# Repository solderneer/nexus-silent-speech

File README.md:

# Nexus, a session-independent silent speech interface
A novel approach to session-independent silent speech recognition systems with a multiplexed star electrode array, developed for my final year dissertation at University College London (UCL). Includes datasets, code, and electronics CAD files.

## Overview
This repository houses my final year dissertation project at University College London (UCL), focused on developing a novel multiplexed star electrode array to address the challenges of cross-session variability in silent speech recognition systems. This innovative approach leverages configurable electrode orientations to significantly enhance the signal-to-noise ratio (SNR) of surface electromyography (sEMG) signals, leading to improved recognition accuracy across sessions.

## Project Objectives
- To investigate the impact of cross-session variability on the accuracy of silent speech recognition systems.
- To design, develop, and evaluate a multiplexed star electrode array capable of adjusting electrode orientations for optimal muscle-electrode alignment.
- To compare the performance of the novel star electrode array against traditional electrode configurations in terms of SNR and silent speech recognition accuracy.

## Results Summary
The project successfully demonstrated the potential of the star electrode array to achieve superior muscle-electrode alignment, resulting in a significant increase in SNR compared to control configurations. Most notably, the array displayed a remarkable 41% relative improvement in cross-session classification accuracy, underscoring its effectiveness in mitigating the challenges posed by session-dependent variability.

## Contents
- `datasets/`: Contains the sEMG datasets collected during the project, across multiple sessions and with different electrode configurations.
- `code/`: Includes all code developed for signal acquisition, signal processing, feature extraction, and classification tasks.
- `cad/`: Houses the electronics CAD files for the star electrode array and control circuitry, enabling replication and further research.
- `docs/`: Additional project documentation, including project report and presentation slides.

## Contact
For any inquiries or collaboration proposals, please contact [Shan](https://solderneer.me) at [sudhar393@gmail.com](mailto://sudhar393@gmail.com).

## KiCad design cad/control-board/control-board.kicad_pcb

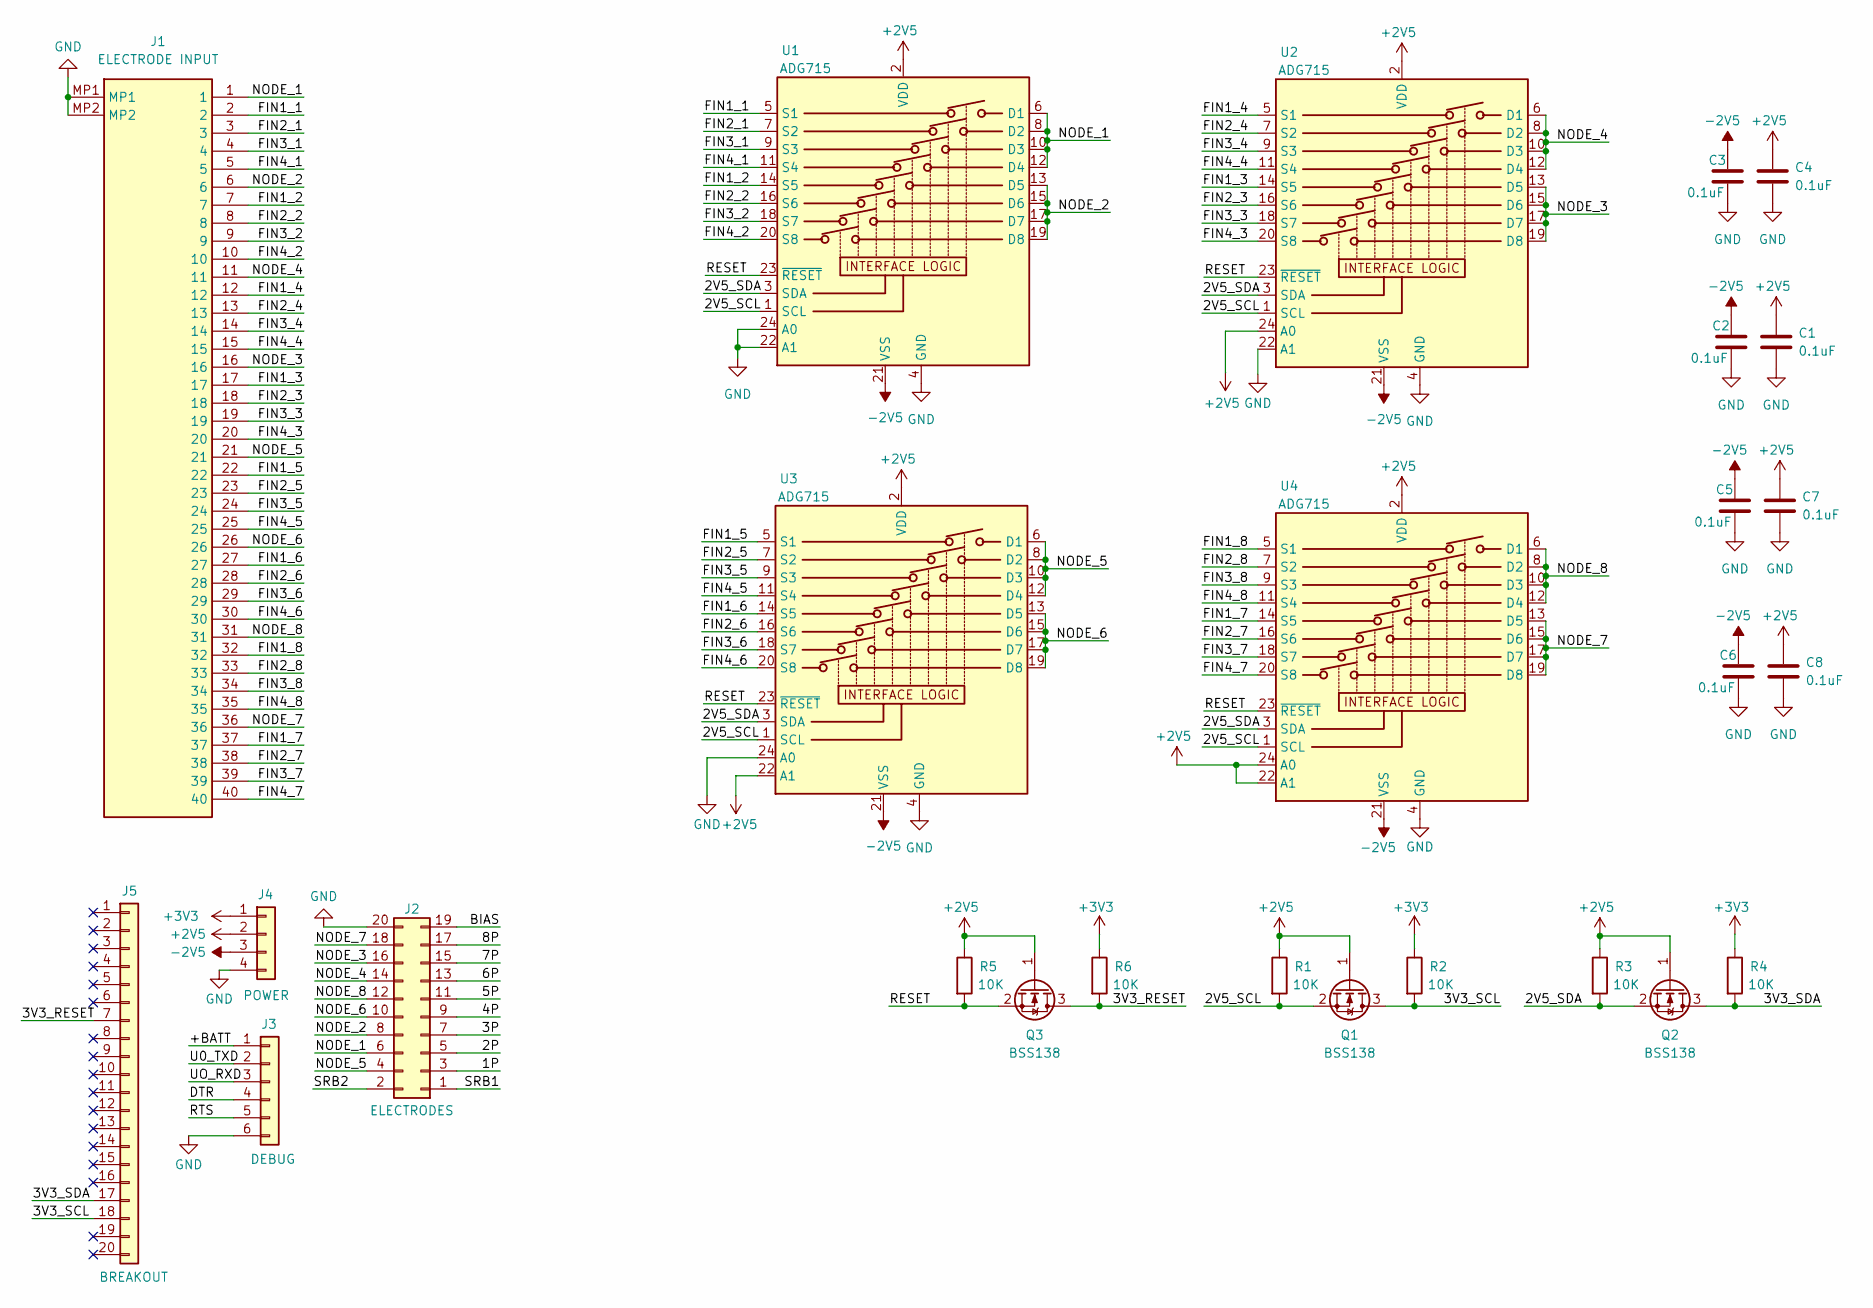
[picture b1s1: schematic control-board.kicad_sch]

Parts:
C1, C2, C3, C4, C5, C6, C7, C8: 0.1uF; C_0603_1608Metric
J1: ELECTRODE INPUT; F32D1A7Y121040; Manufacturer_Part_Number F32D-1A7Y1-21040
J2: ELECTRODES; PinHeader_2x10_P2.54mm_Vertical
J3: DEBUG; PinHeader_1x06_P2.54mm_Vertical
J4: POWER; PinHeader_1x04_P2.54mm_Vertical
J5: BREAKOUT; PinHeader_1x20_P2.54mm_Vertical
Q1, Q2, Q3: BSS138; SOT-23
R1, R2, R3, R4, R5, R6: 10K; R_0603_1608Metric
U1, U2, U3, U4: ADG715; TSSOP-24_4.4x7.8mm_P0.65mm

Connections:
+2V5: C1.1, C4.1, C7.1, C8.1, J4.2, Q1.1 (G), Q2.1 (G), Q3.1 (G), R1.1, R3.1, R5.1, U1.2 (VDD), U2.2 (VDD), U2.24 (A0), U3.2 (VDD), U3.22 (A1), U4.2 (VDD), U4.22 (A1), U4.24 (A0)
+3V3: J4.1, R2.1, R4.1, R6.1
-2V5: C2.1, C3.1, C5.1, C6.1, J4.3, U1.21 (VSS), U2.21 (VSS), U3.21 (VSS), U4.21 (VSS)
/1P: J2.3
/2P: J2.5
/2V5_SCL: Q1.2 (S), R1.2, U1.1 (SCL), U2.1 (SCL), U3.1 (SCL), U4.1 (SCL)
/2V5_SDA: Q2.2 (S), R3.2, U1.3 (SDA), U2.3 (SDA), U3.3 (SDA), U4.3 (SDA)
/3P: J2.7
/3V3_RESET: J5.7, Q3.3 (D), R6.2
/3V3_SCL: J5.18, Q1.3 (D), R2.2
/3V3_SDA: J5.17, Q2.3 (D), R4.2
/4P: J2.9
/5P: J2.11
/6P: J2.13
/7P: J2.15
/8P: J2.17
/+BATT: J3.1
/BIAS: J2.19
/DTR: J3.4
/FIN1_1: J1.2, U1.5 (S1)
/FIN1_2: J1.7, U1.14 (S5)
/FIN1_3: J1.17, U2.14 (S5)
/FIN1_4: J1.12, U2.5 (S1)
/FIN1_5: J1.22, U3.5 (S1)
/FIN1_6: J1.27, U3.14 (S5)
/FIN1_7: J1.37, U4.14 (S5)
/FIN1_8: J1.32, U4.5 (S1)
/FIN2_1: J1.3, U1.7 (S2)
/FIN2_2: J1.8, U1.16 (S6)
/FIN2_3: J1.18, U2.16 (S6)
/FIN2_4: J1.13, U2.7 (S2)
/FIN2_5: J1.23, U3.7 (S2)
/FIN2_6: J1.28, U3.16 (S6)
/FIN2_7: J1.38, U4.16 (S6)
/FIN2_8: J1.33, U4.7 (S2)
/FIN3_1: J1.4, U1.9 (S3)
/FIN3_2: J1.9, U1.18 (S7)
/FIN3_3: J1.19, U2.18 (S7)
/FIN3_4: J1.14, U2.9 (S3)
/FIN3_5: J1.24, U3.9 (S3)
/FIN3_6: J1.29, U3.18 (S7)
/FIN3_7: J1.39, U4.18 (S7)
/FIN3_8: J1.34, U4.9 (S3)
/FIN4_1: J1.5, U1.11 (S4)
/FIN4_2: J1.10, U1.20 (S8)
/FIN4_3: J1.20, U2.20 (S8)
/FIN4_4: J1.15, U2.11 (S4)
/FIN4_5: J1.25, U3.11 (S4)
/FIN4_6: J1.30, U3.20 (S8)
/FIN4_7: J1.40, U4.20 (S8)
/FIN4_8: J1.35, U4.11 (S4)
/NODE_1: J1.1, J2.6, U1.6 (D1), U1.8 (D2), U1.10 (D3), U1.12 (D4)
/NODE_2: J1.6, J2.8, U1.13 (D5), U1.15 (D6), U1.17 (D7), U1.19 (D8)
/NODE_3: J1.16, J2.16, U2.13 (D5), U2.15 (D6), U2.17 (D7), U2.19 (D8)
/NODE_4: J1.11, J2.14, U2.6 (D1), U2.8 (D2), U2.10 (D3), U2.12 (D4)
/NODE_5: J1.21, J2.4, U3.6 (D1), U3.8 (D2), U3.10 (D3), U3.12 (D4)
/NODE_6: J1.26, J2.10, U3.13 (D5), U3.15 (D6), U3.17 (D7), U3.19 (D8)
/NODE_7: J1.36, J2.18, U4.13 (D5), U4.15 (D6), U4.17 (D7), U4.19 (D8)
/NODE_8: J1.31, J2.12, U4.6 (D1), U4.8 (D2), U4.10 (D3), U4.12 (D4)
/RESET: Q3.2 (S), R5.2, U1.23 (~RESET), U2.23 (~RESET), U3.23 (~RESET), U4.23 (~RESET)
/RTS: J3.5
/SRB1: J2.1
/SRB2: J2.2
/U0_TXD: J3.2
/UO_RXD: J3.3
GND: C1.2, C2.2, C3.2, C4.2, C5.2, C6.2, C7.2, C8.2, J1.MP1, J1.MP2, J2.20, J3.6, J4.4, U1.4 (GND), U1.22 (A1), U1.24 (A0), U2.4 (GND), U2.22 (A1), U3.4 (GND), U3.24 (A0), U4.4 (GND)

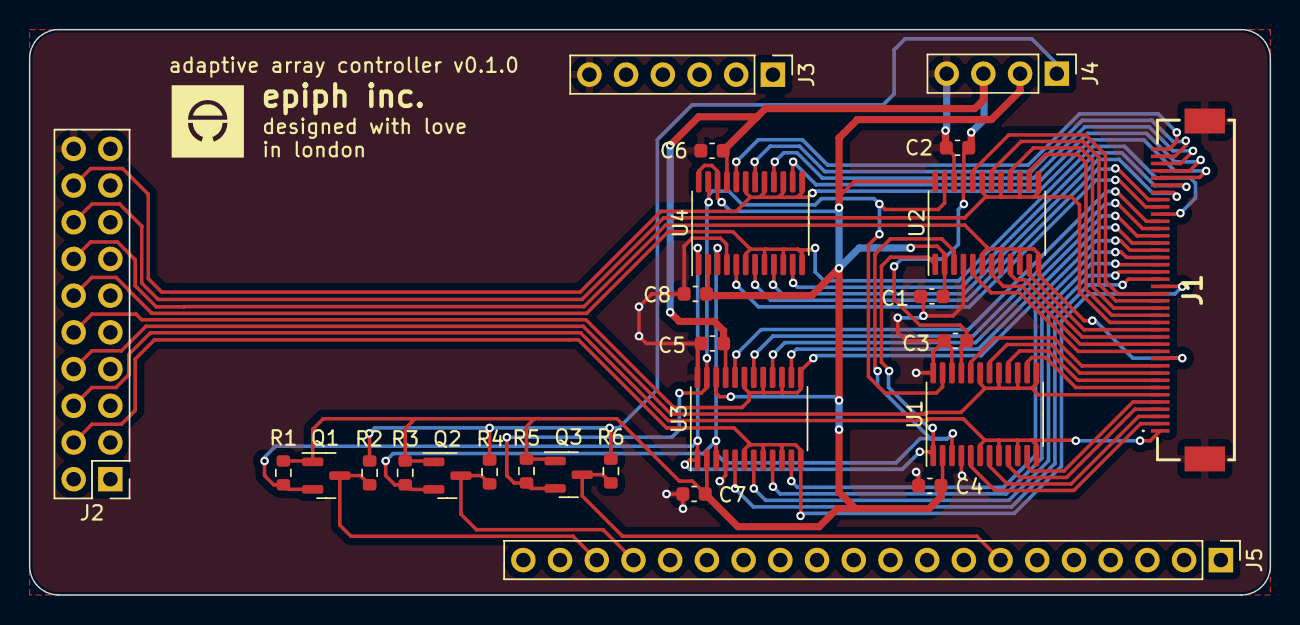
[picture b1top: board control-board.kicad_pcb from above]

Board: 2 copper layers, 85.9 x 39.1 mm, 26 parts (0 on the bottom side), 50 nets.

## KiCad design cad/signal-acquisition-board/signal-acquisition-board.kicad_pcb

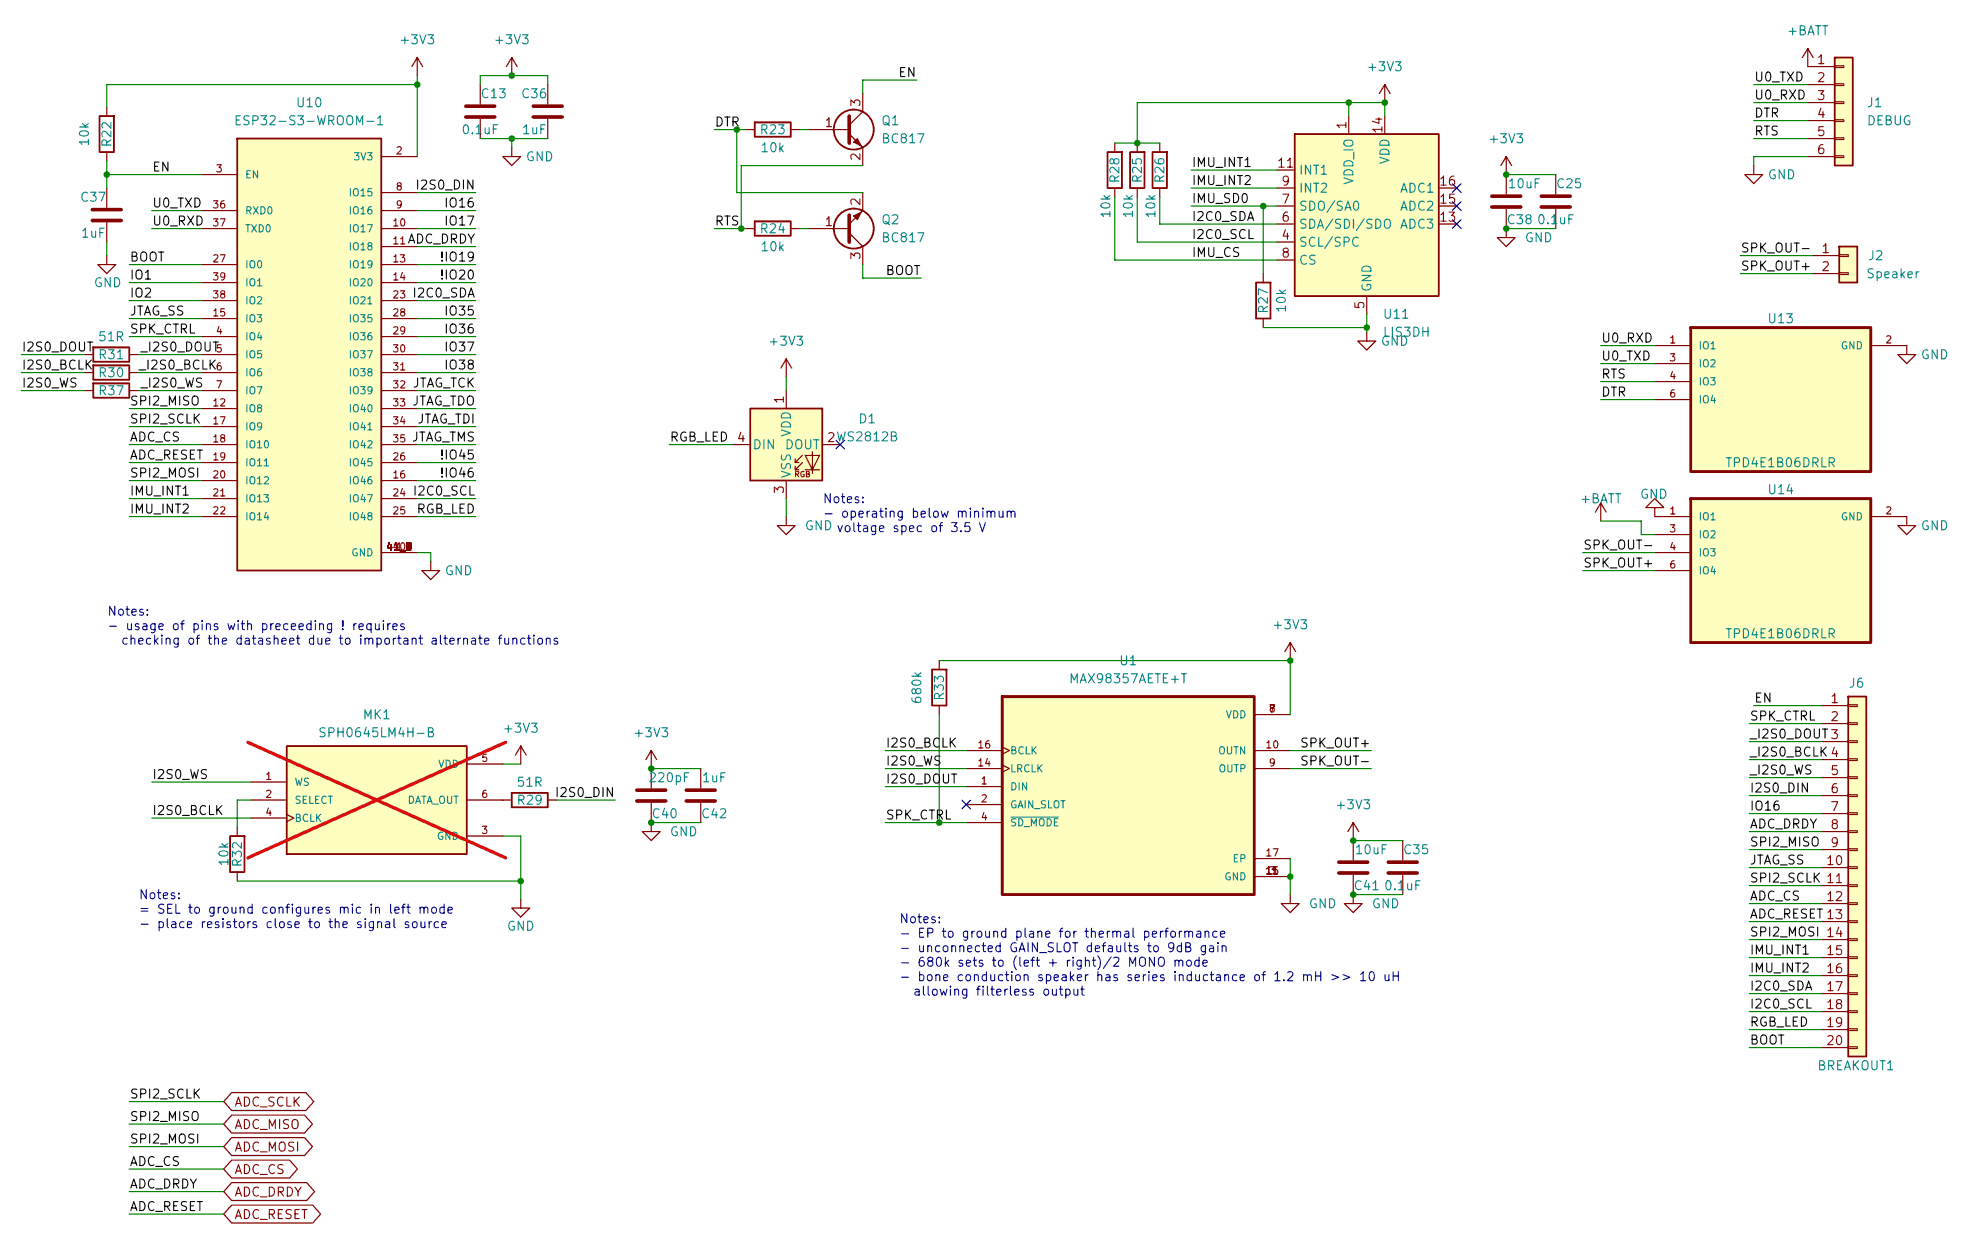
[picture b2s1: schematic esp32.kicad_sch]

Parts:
C13, C25, C35: 0.1uF; C_0402_1005Metric; Manufacturer Part No. 0402ZD104KAT2A; JLCPCB Part No. C2649532
C36, C37, C42: 1uF; C_0402_1005Metric; Manufacturer Part No. CC0402MRX5R6BB105; JLCPCB Part No. C113791
C38, C41: 10uF; C_0603_1608Metric; Manufacturer Part No. 0603X106M100NT; JLCPCB Part No. C91150
C40: 220pF; C_0402_1005Metric; Manufacturer Part No. C1005X7R221KGT; JLCPCB Part No. C424337
D1: WS2812B; LED_WS2812B_PLCC4_5.0x5.0mm_P3.2mm; Manufacturer Part No. WS2812B-B/T; JLCPCB Part No. C2761795
J1: DEBUG; PinHeader_1x06_P2.54mm_Vertical
J2: Speaker; PinHeader_1x02_P2.54mm_Vertical
J6: BREAKOUT1; PinHeader_1x20_P2.54mm_Vertical
MK1: SPH0645LM4H-B; MIC_SPH0645LM4H-B; Manufacturer Part No. SPH0645LM4H-B-8; JLCPCB Part No. C19190864; not fitted
Q1, Q2: BC817; SOT-23; Manufacturer Part No. BC817; JLCPCB Part No. C475629
R22, R23, R24, R25, R26, R27, R28, R32: 10k; R_0402_1005Metric; Manufacturer Part No. 0402WGF1002TCE; JLCPCB Part No. C25744
R29, R30, R31, R37: 51R; R_0402_1005Metric; Manufacturer Part No. CR-02FL6---51R; JLCPCB Part No. C279983
R33: 680k; R_0402_1005Metric; Manufacturer Part No. RMC10K684FTH; JLCPCB Part No. C323627
U1: MAX98357AETE+T; Manufacturer Part No. MAX98357AETE+T; JLCPCB Part No. C910544
U10: ESP32-S3-WROOM-1; Manufacturer Part No. ESP32-S3-WROOM-1(N8R8); JLCPCB Part No. C2913201
U11: LIS3DH; LGA-16_3x3mm_P0.5mm_LayoutBorder3x5y; Manufacturer Part No. LIS3DHTR; JLCPCB Part No. C15134
U13, U14: TPD4E1B06DRLR; Manufacturer Part No. TPD4E1B06DRLR; JLCPCB Part No. C1972953

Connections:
+3V3: C13.2, C25.2, C35.2, C36.1, C38.1, C40.1, C41.1, C42.1, D1.1 (VDD), MK1.5 (VDD), R22.2, R25.2, R26.2, R28.2, R33.2, U1.7 (VDD), U1.8 (VDD), U10.2 (3V3), U11.1 (VDD_IO), U11.14 (VDD); also elsewhere on the board
+BATT: J1.1, U14.3 (IO2); also elsewhere on the board
/mcu/!IO19: U10.13 (IO19)
/mcu/!IO20: U10.14 (IO20)
/mcu/!IO45: U10.26 (IO45)
/mcu/!IO46: U10.16 (IO46)
/mcu/BOOT: J6.20, Q2.3 (C), U10.27 (IO0)
/mcu/DTR: J1.4, Q2.2 (E), R23.2, U13.6 (IO4)
/mcu/EN: C37.1, J6.1, Q1.3 (C), R22.1, U10.3 (EN)
/mcu/I2C0_SCL: J6.18, R25.1, U10.24 (IO47), U11.4 (SCL/SPC)
/mcu/I2C0_SDA: J6.17, R26.1, U10.23 (IO21), U11.6 (SDA/SDI/SDO)
/mcu/I2S0_BCLK: MK1.4 (BCLK), R30.2, U1.16 (BCLK)
/mcu/I2S0_DIN: J6.6, R29.1, U10.8 (IO15)
/mcu/I2S0_DOUT: R31.2, U1.1 (DIN)
/mcu/I2S0_WS: MK1.1 (WS), R37.2, U1.14 (LRCLK)
/mcu/IMU_CS: R28.1, U11.8 (CS)
/mcu/IMU_INT1: J6.15, U10.21 (IO13), U11.11 (INT1)
/mcu/IMU_INT2: J6.16, U10.22 (IO14), U11.9 (INT2)
/mcu/IMU_SD0: R27.2, U11.7 (SDO/SA0)
/mcu/IO1: U10.39 (IO1)
/mcu/IO2: U10.38 (IO2)
/mcu/IO16: J6.7, U10.9 (IO16)
/mcu/IO17: U10.10 (IO17)
/mcu/IO35: U10.28 (IO35)
/mcu/IO36: U10.29 (IO36)
/mcu/IO37: U10.30 (IO37)
/mcu/IO38: U10.31 (IO38)
/mcu/JTAG_SS: J6.10, U10.15 (IO3)
/mcu/JTAG_TCK: U10.32 (IO39)
/mcu/JTAG_TDI: U10.34 (IO41)
/mcu/JTAG_TDO: U10.33 (IO40)
/mcu/JTAG_TMS: U10.35 (IO42)
/mcu/RGB_LED: D1.4 (DIN), J6.19, U10.25 (IO48)
/mcu/RTS: J1.5, Q1.2 (E), R24.2, U13.4 (IO3)
/mcu/SPK_CTRL: J6.2, R33.1, U1.4 (~SD_MODE), U10.4 (IO4)
/mcu/SPK_OUT+: J2.2, U1.10 (OUTN), U14.6 (IO4)
/mcu/SPK_OUT-: J2.1, U1.9 (OUTP), U14.4 (IO3)
/mcu/U0_RXD: J1.3, U10.37 (TXD0), U13.1 (IO1)
/mcu/U0_TXD: J1.2, U10.36 (RXD0), U13.3 (IO2)
/mcu/_I2S0_BCLK: J6.4, R30.1, U10.6 (IO6)
/mcu/_I2S0_DOUT: J6.3, R31.1, U10.5 (IO5)
/mcu/_I2S0_WS: J6.5, R37.1, U10.7 (IO7)
ADC_CS: J6.12, U10.18 (IO10); also elsewhere on the board
ADC_DRDY: J6.8, U10.11 (IO18); also elsewhere on the board
ADC_MISO: J6.9, U10.12 (IO8); also elsewhere on the board
ADC_MOSI: J6.14, U10.20 (IO12); also elsewhere on the board
ADC_RESET: J6.13, U10.19 (IO11); also elsewhere on the board
ADC_SCLK: J6.11, U10.17 (IO9); also elsewhere on the board
GND: C13.1, C25.1, C35.1, C36.2, C37.2, C38.2, C40.2, C41.2, C42.2, D1.3 (VSS), J1.6, MK1.3 (GND), R27.1, R32.1, U1.3 (GND), U1.11 (GND), U1.15 (GND), U1.17 (EP), U10.1 (GND), U10.40 (GND), U10.41_1 (GND), U10.41_2 (GND), U10.41_3 (GND), U10.41_4 (GND), U10.41_5 (GND), U10.41_6 (GND), U10.41_7 (GND), U10.41_8 (GND), U10.41_9 (GND), U11.5 (GND), U11.10 (GND), U11.12 (GND), U13.2 (GND), U14.1 (IO1), U14.2 (GND); also elsewhere on the board
unnamed: MK1.6 (DATA_OUT), R29.2
unnamed: MK1.2 (SELECT), R32.2
unnamed: Q1.1 (B), R23.1
unnamed: Q2.1 (B), R24.1

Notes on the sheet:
Notes: = SEL to ground configures mic in left mode - place resistors close to the signal source
Notes: - EP to ground plane for thermal performance - unconnected GAIN_SLOT defaults to 9dB gain - 680k sets to (left + right)/2 MONO mode - bone conduction speaker has series inductance of 1.2 mH >> 10 uH allowing filterless output
Notes: - usage of pins with preceeding ! requires checking of the datasheet due to important alternate functions
Notes: - operating below minimum voltage spec of 3.5 V

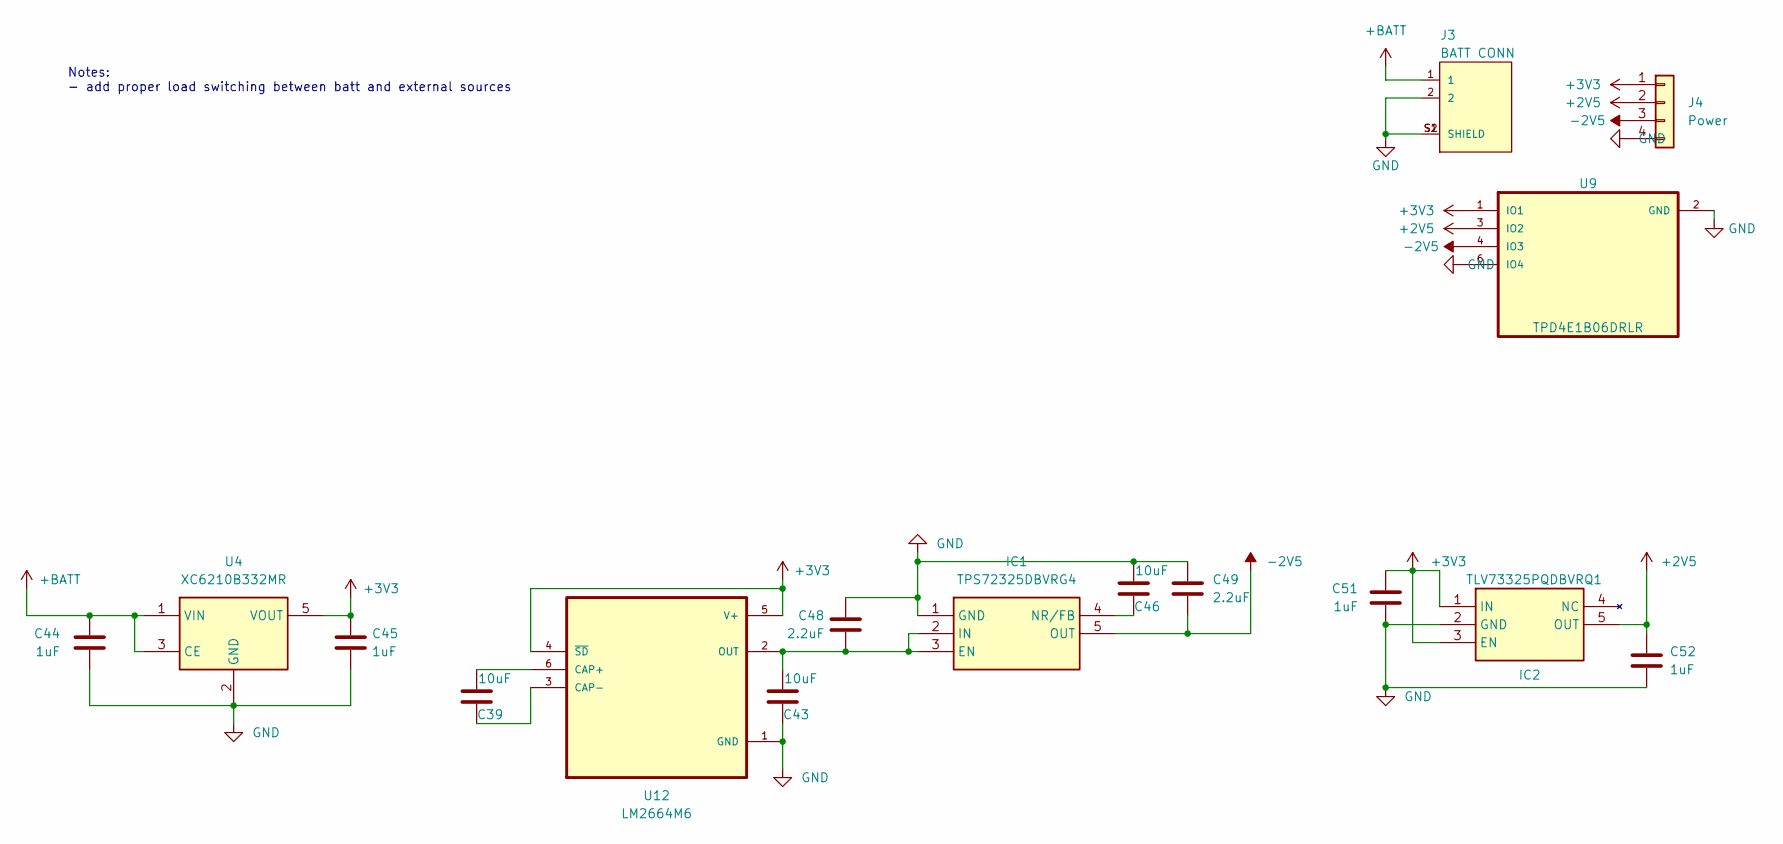
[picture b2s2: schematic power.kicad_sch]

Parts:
C39, C43, C46: 10uF; C_0603_1608Metric; Manufacturer Part No. 0603X106M100NT; JLCPCB Part No. C91150
C44: 1uF; C_0402_1005Metric; Manufacturer Part No. GRM188R71E105KA12D; JLCPCB Part No. C86020
C45, C51, C52: 1uF; C_0402_1005Metric; Manufacturer Part No. CC0402MRX5R6BB105; JLCPCB Part No. C113791
C48, C49: 2.2uF; C_0402_1005Metric; Manufacturer Part No. GRM155Z71A225KE44D; JLCPCB Part No. C2999759
IC1: TPS72325DBVRG4; Manufacturer Part No. TPS72325DBVRG4; JLCPCB Part No. C3746858
IC2: TLV73325PQDBVRQ1; Manufacturer Part No. TLV73325PQDBVRQ1; JLCPCB Part No. C2860807
J3: BATT CONN; JST_S2B-PH-SM4-TB_LF__SN_; Manufacturer Part No. S2B-PH-SM4-TB(LF)(SN); JLCPCB Part No. C295747
J4: Power; PinHeader_1x04_P2.54mm_Vertical
U4: XC6210B332MR; SOT-23-5; Manufacturer Part No. XC6210B332MR; JLCPCB Part No. C3021084
U9: TPD4E1B06DRLR; Manufacturer Part No. TPD4E1B06DRLR; JLCPCB Part No. C1972953
U12: LM2664M6; Manufacturer Part No. LM2664M6/NOPB; JLCPCB Part No. C840095

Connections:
+2V5: C52.1, IC2.5 (OUT), J4.2, U9.3 (IO2); also elsewhere on the board
+3V3: C45.1, C51.1, IC2.1 (IN), IC2.3 (EN), J4.1, U4.5 (VOUT), U9.1 (IO1), U12.4 (~SD), U12.5 (V+); also elsewhere on the board
+BATT: C44.1, J3.1, U4.1 (VIN), U4.3 (CE); also elsewhere on the board
-2V5: C49.2, IC1.5 (OUT), J4.3, U9.4 (IO3); also elsewhere on the board
GND: C43.2, C44.2, C45.2, C46.1, C48.1, C49.1, C51.2, C52.2, IC1.1 (GND), IC2.2 (GND), J3.2, J3.S1 (SHIELD), J3.S2 (SHIELD), J4.4, U4.2 (GND), U9.2 (GND), U9.6 (IO4), U12.1 (GND); also elsewhere on the board
unnamed: C43.1, C48.2, IC1.2 (IN), IC1.3 (EN), U12.2 (OUT)
unnamed: C46.2, IC1.4 (NR/FB)
unnamed: C39.1, U12.6 (CAP+)
unnamed: C39.2, U12.3 (CAP-)

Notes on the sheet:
Notes: - add proper load switching between batt and external sources

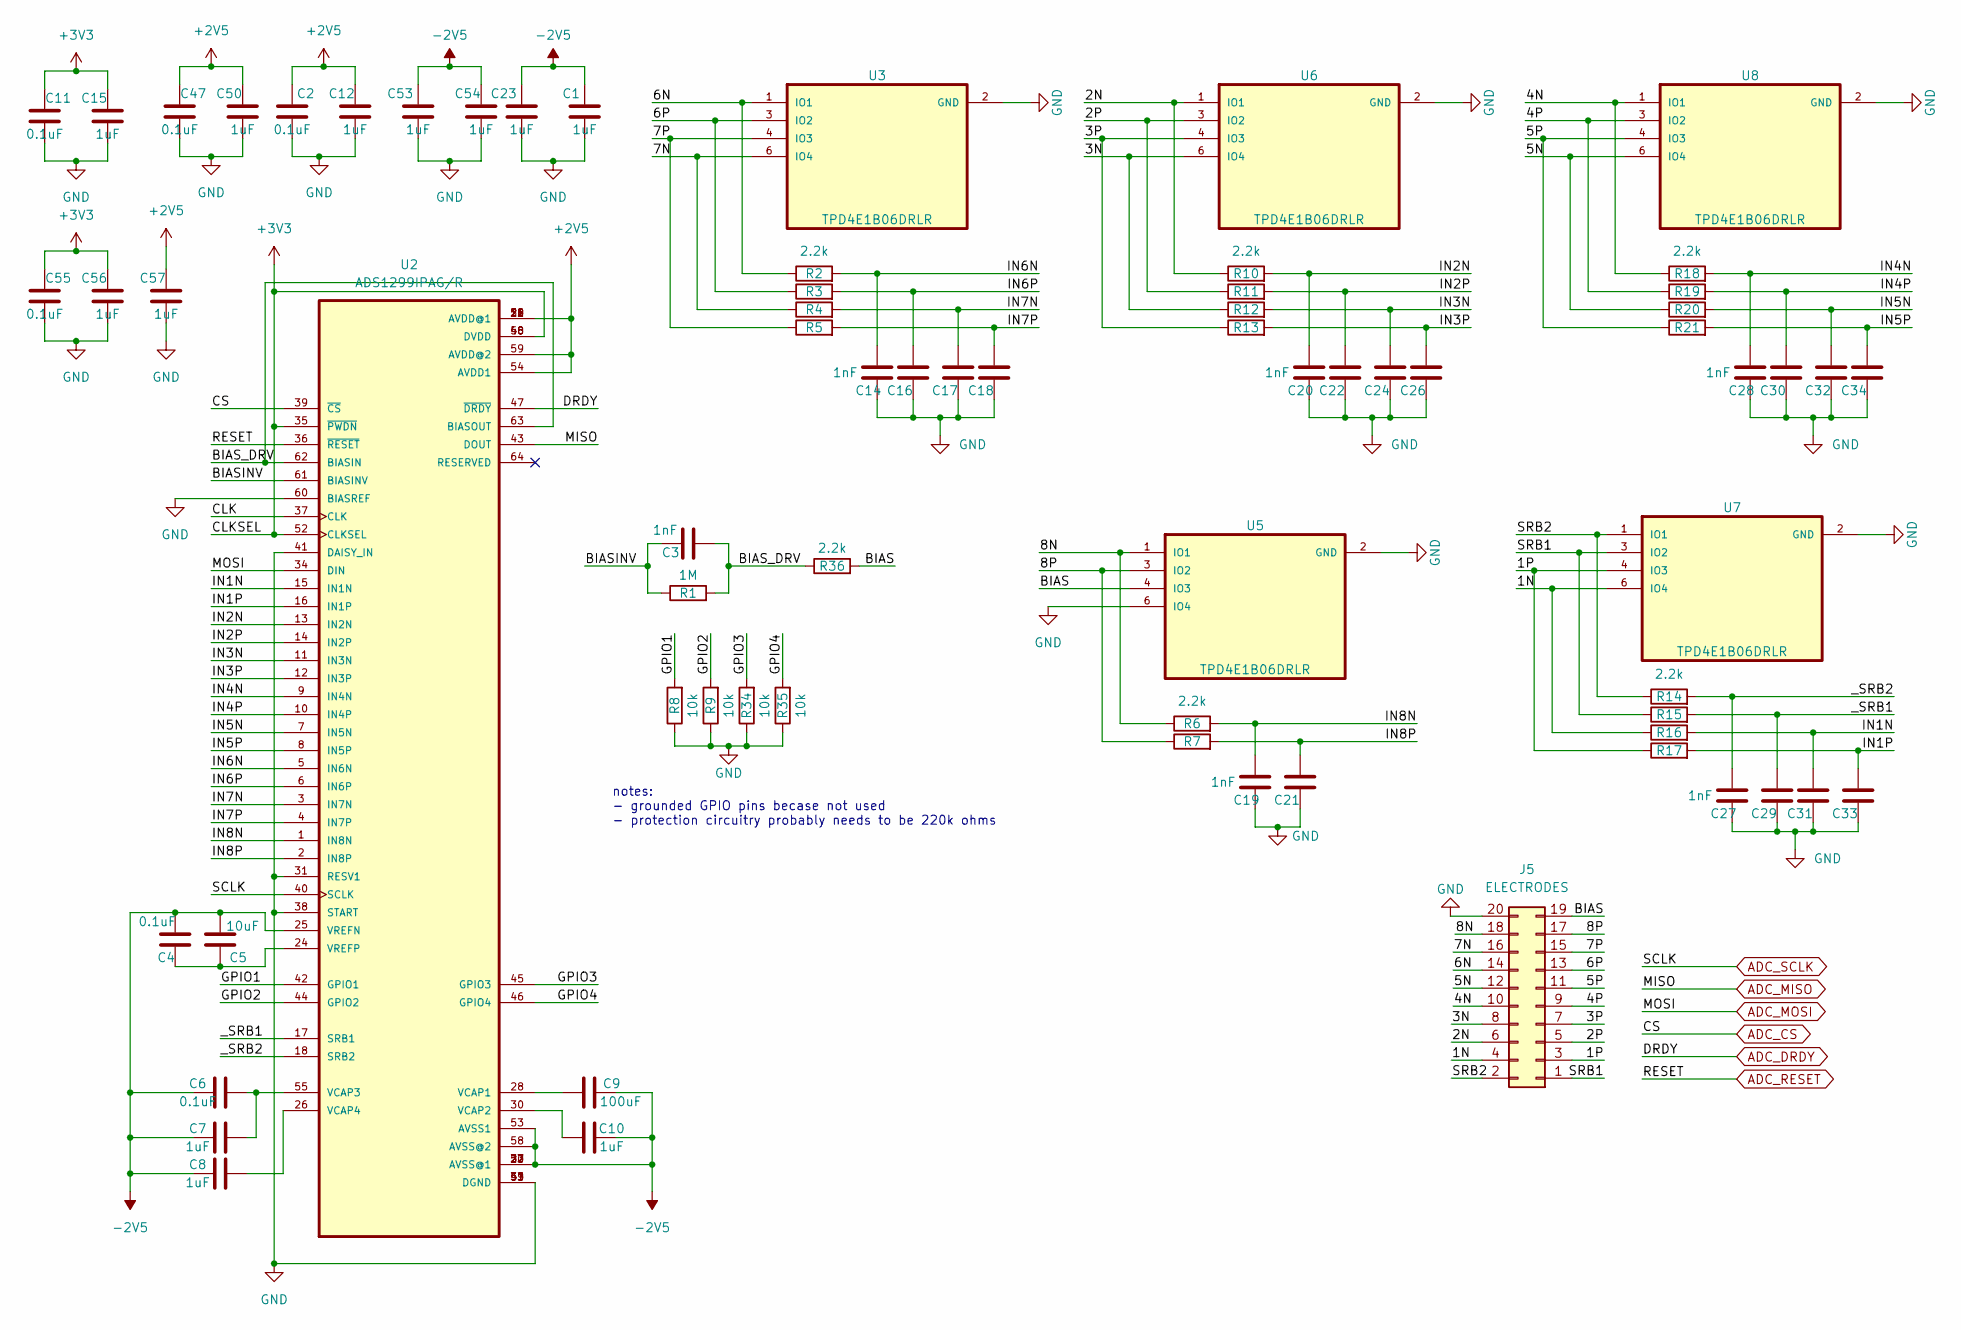
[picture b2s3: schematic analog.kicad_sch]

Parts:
C1, C7, C8, C10, C12, C15, C23, C50, C53, C54, C56, C57: 1uF; C_0402_1005Metric; Manufacturer Part No. CC0402MRX5R6BB105; JLCPCB Part No. C113791
C2, C4, C6, C11, C47, C55: 0.1uF; C_0402_1005Metric; Manufacturer Part No. 0402ZD104KAT2A; JLCPCB Part No. C2649532
C3, C14, C16, C17, C18, C19, C20, C21, C22, C24, C26, C27, C28, C29, C30, C31, C32, C33, C34: 1nF; C_0402_1005Metric; Manufacturer Part No. GCM1555C1H102FA16D; JLCPCB Part No. C126493
C5: 10uF; C_0402_1005Metric; Manufacturer Part No. GRM155C80J106ME11D; JLCPCB Part No. C237279
C9: 100uF; C_1206_3216Metric; Manufacturer Part No. CL31A107MPKNNWE; JLCPCB Part No. C7588440
J5: ELECTRODES; PinHeader_2x10_P2.54mm_Vertical
R1: 1M; R_0402_1005Metric; Manufacturer Part No. CR-02FL6----1M; JLCPCB Part No. C409676
R2, R3, R4, R5, R6, R7, R10, R11, R12, R13, R14, R15, R16, R17, R18, R19, R20, R21, R36: 2.2k; R_0402_1005Metric; Manufacturer Part No. RMC04022.2K1%N; JLCPCB Part No. C325418
R8, R9, R34, R35: 10k; R_0402_1005Metric; Manufacturer Part No. 0402WGF1002TCE; JLCPCB Part No. C25744
U2: ADS1299IPAG/R; ADS1299IPAG; Manufacturer Part No. ADS1299IPAGR; JLCPCB Part No. C476817
U3, U5, U6, U7, U8: TPD4E1B06DRLR; Manufacturer Part No. TPD4E1B06DRLR; JLCPCB Part No. C1972953

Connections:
+2V5: C2.1, C12.1, C47.1, C50.1, C57.1, U2.19 (AVDD@1), U2.21 (AVDD@1), U2.22 (AVDD@1), U2.54 (AVDD1), U2.56 (AVDD@1), U2.59 (AVDD@2); also elsewhere on the board
+3V3: C11.1, C15.1, C55.1, C56.1, U2.35 (~PWDN), U2.48 (DVDD), U2.50 (DVDD), U2.52 (CLKSEL); also elsewhere on the board
-2V5: C1.1, C4.1, C5.1, C6.1, C7.1, C8.1, C9.2, C10.2, C23.1, C53.1, C54.1, U2.20 (AVSS@1), U2.23 (AVSS@1), U2.25 (VREFN), U2.32 (AVSS@1), U2.53 (AVSS1), U2.57 (AVSS@1), U2.58 (AVSS@2); also elsewhere on the board
/analog/1N: J5.4, R16.1, U7.6 (IO4)
/analog/1P: J5.3, R17.1, U7.4 (IO3)
/analog/2N: J5.6, R10.1, U6.1 (IO1)
/analog/2P: J5.5, R11.1, U6.3 (IO2)
/analog/3N: J5.8, R12.1, U6.6 (IO4)
/analog/3P: J5.7, R13.1, U6.4 (IO3)
/analog/4N: J5.10, R18.1, U8.1 (IO1)
/analog/4P: J5.9, R19.1, U8.3 (IO2)
/analog/5N: J5.12, R20.1, U8.6 (IO4)
/analog/5P: J5.11, R21.1, U8.4 (IO3)
/analog/6N: J5.14, R2.1, U3.1 (IO1)
/analog/6P: J5.13, R3.1, U3.3 (IO2)
/analog/7N: J5.16, R4.1, U3.6 (IO4)
/analog/7P: J5.15, R5.1, U3.4 (IO3)
/analog/8N: J5.18, R6.1, U5.1 (IO1)
/analog/8P: J5.17, R7.1, U5.3 (IO2)
/analog/BIAS: J5.19, R36.2, U5.4 (IO3)
/analog/BIASINV: C3.2, R1.1, U2.61 (BIASINV)
/analog/BIAS_DRV: C3.1, R1.2, R36.1, U2.62 (BIASIN), U2.63 (BIASOUT)
/analog/CLK: U2.37 (CLK)
/analog/GPIO1: R8.2, U2.42 (GPIO1)
/analog/GPIO2: R9.2, U2.44 (GPIO2)
/analog/GPIO3: R34.2, U2.45 (GPIO3)
/analog/GPIO4: R35.2, U2.46 (GPIO4)
/analog/IN1N: C31.1, R16.2, U2.15 (IN1N)
/analog/IN1P: C33.1, R17.2, U2.16 (IN1P)
/analog/IN2N: C20.1, R10.2, U2.13 (IN2N)
/analog/IN2P: C22.1, R11.2, U2.14 (IN2P)
/analog/IN3N: C24.1, R12.2, U2.11 (IN3N)
/analog/IN3P: C26.1, R13.2, U2.12 (IN3P)
/analog/IN4N: C28.1, R18.2, U2.9 (IN4N)
/analog/IN4P: C30.1, R19.2, U2.10 (IN4P)
/analog/IN5N: C32.1, R20.2, U2.7 (IN5N)
/analog/IN5P: C34.1, R21.2, U2.8 (IN5P)
/analog/IN6N: C14.1, R2.2, U2.5 (IN6N)
/analog/IN6P: C16.1, R3.2, U2.6 (IN6P)
/analog/IN7N: C17.1, R4.2, U2.3 (IN7N)
/analog/IN7P: C18.1, R5.2, U2.4 (IN7P)
/analog/IN8N: C19.1, R6.2, U2.1 (IN8N)
/analog/IN8P: C21.1, R7.2, U2.2 (IN8P)
/analog/SRB1: J5.1, R15.1, U7.3 (IO2)
/analog/SRB2: J5.2, R14.1, U7.1 (IO1)
/analog/_SRB1: C29.1, R15.2, U2.17 (SRB1)
/analog/_SRB2: C27.1, R14.2, U2.18 (SRB2)
ADC_CS: U2.39 (~CS); also elsewhere on the board
ADC_DRDY: U2.47 (~DRDY); also elsewhere on the board
ADC_MISO: U2.43 (DOUT); also elsewhere on the board
ADC_MOSI: U2.34 (DIN); also elsewhere on the board
ADC_RESET: U2.36 (~RESET); also elsewhere on the board
ADC_SCLK: U2.40 (SCLK); also elsewhere on the board
GND: C1.2, C2.2, C11.2, C12.2, C14.2, C15.2, C16.2, C17.2, C18.2, C19.2, C20.2, C21.2, C22.2, C23.2, C24.2, C26.2, C27.2, C28.2, C29.2, C30.2, C31.2, C32.2, C33.2, C34.2, C47.2, C50.2, C53.2, C54.2, C55.2, C56.2, C57.2, J5.20, R8.1, R9.1, R34.1, R35.1, U2.31 (RESV1), U2.33 (DGND), U2.38 (START), U2.41 (DAISY_IN), U2.49 (DGND), U2.51 (DGND), U2.60 (BIASREF), U3.2 (GND), U5.2 (GND), U5.6 (IO4), U6.2 (GND), U7.2 (GND), U8.2 (GND); also elsewhere on the board
unnamed: C9.1, U2.28 (VCAP1)
unnamed: C10.1, U2.30 (VCAP2)
unnamed: C6.2, C7.2, U2.55 (VCAP3)
unnamed: C8.2, U2.26 (VCAP4)
unnamed: C4.2, C5.2, U2.24 (VREFP)

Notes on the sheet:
notes: - grounded GPIO pins becase not used - protection circuitry probably needs to be 220k ohms

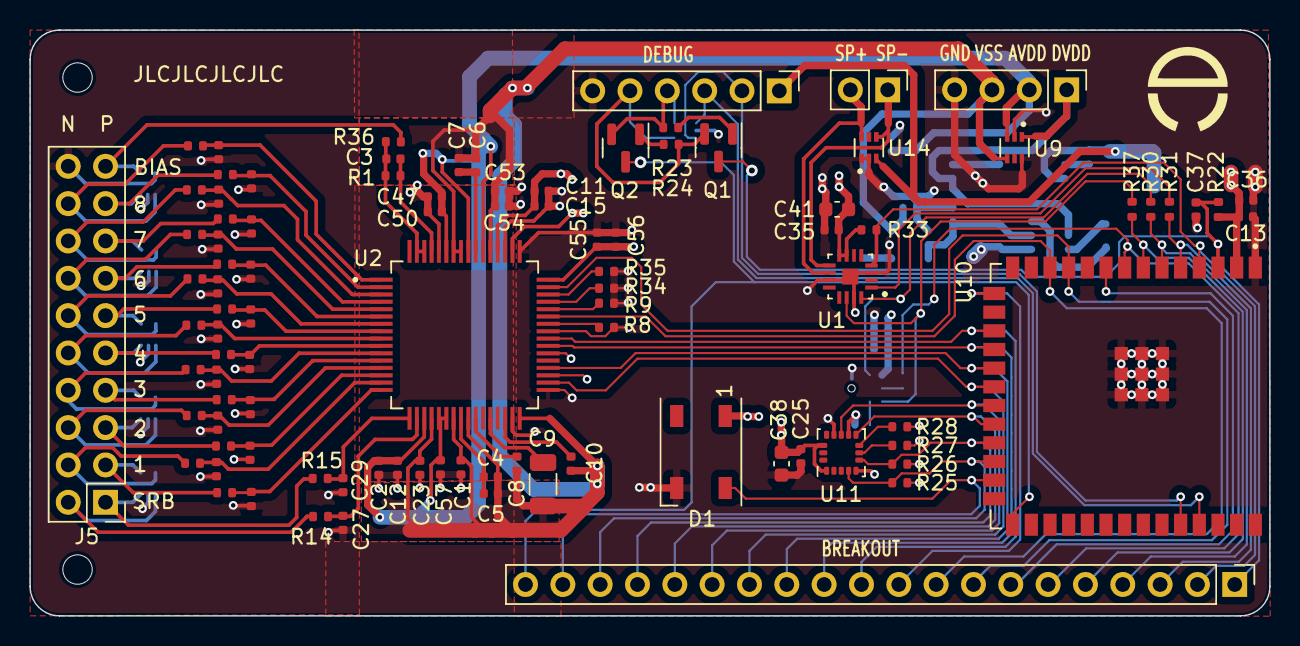
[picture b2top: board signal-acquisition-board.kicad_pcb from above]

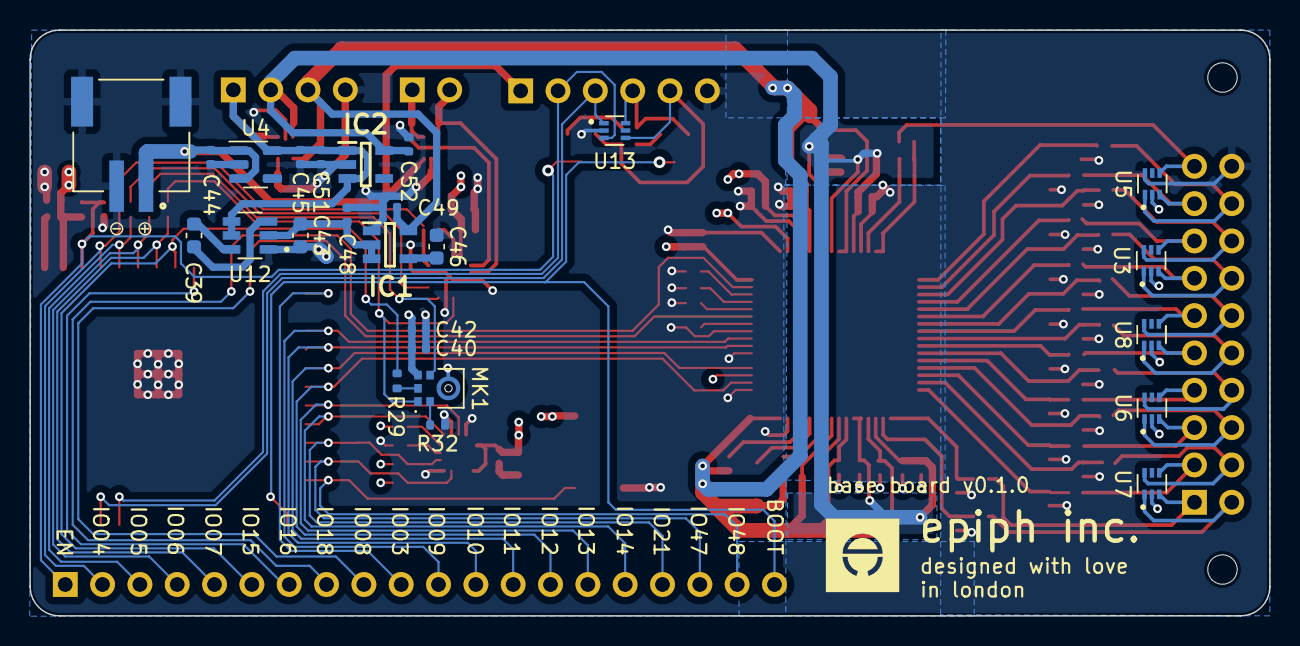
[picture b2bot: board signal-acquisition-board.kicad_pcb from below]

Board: 4 copper layers, 84.4 x 39.9 mm, 120 parts (25 on the bottom side), 92 nets.

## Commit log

2024-04-05 adding final report
